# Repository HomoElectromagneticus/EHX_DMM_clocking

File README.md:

# EHX_DMM_clocking
This is a project to replace the original clock on an EHX Deluxe Memory man with something more capable.

The micro used is a PIC16F18326. It's NCO peripheral will be extremely useful for clock generation.

# License
CC BY-NC-SA https://creativecommons.org/licenses/by-nc-sa/4.0/

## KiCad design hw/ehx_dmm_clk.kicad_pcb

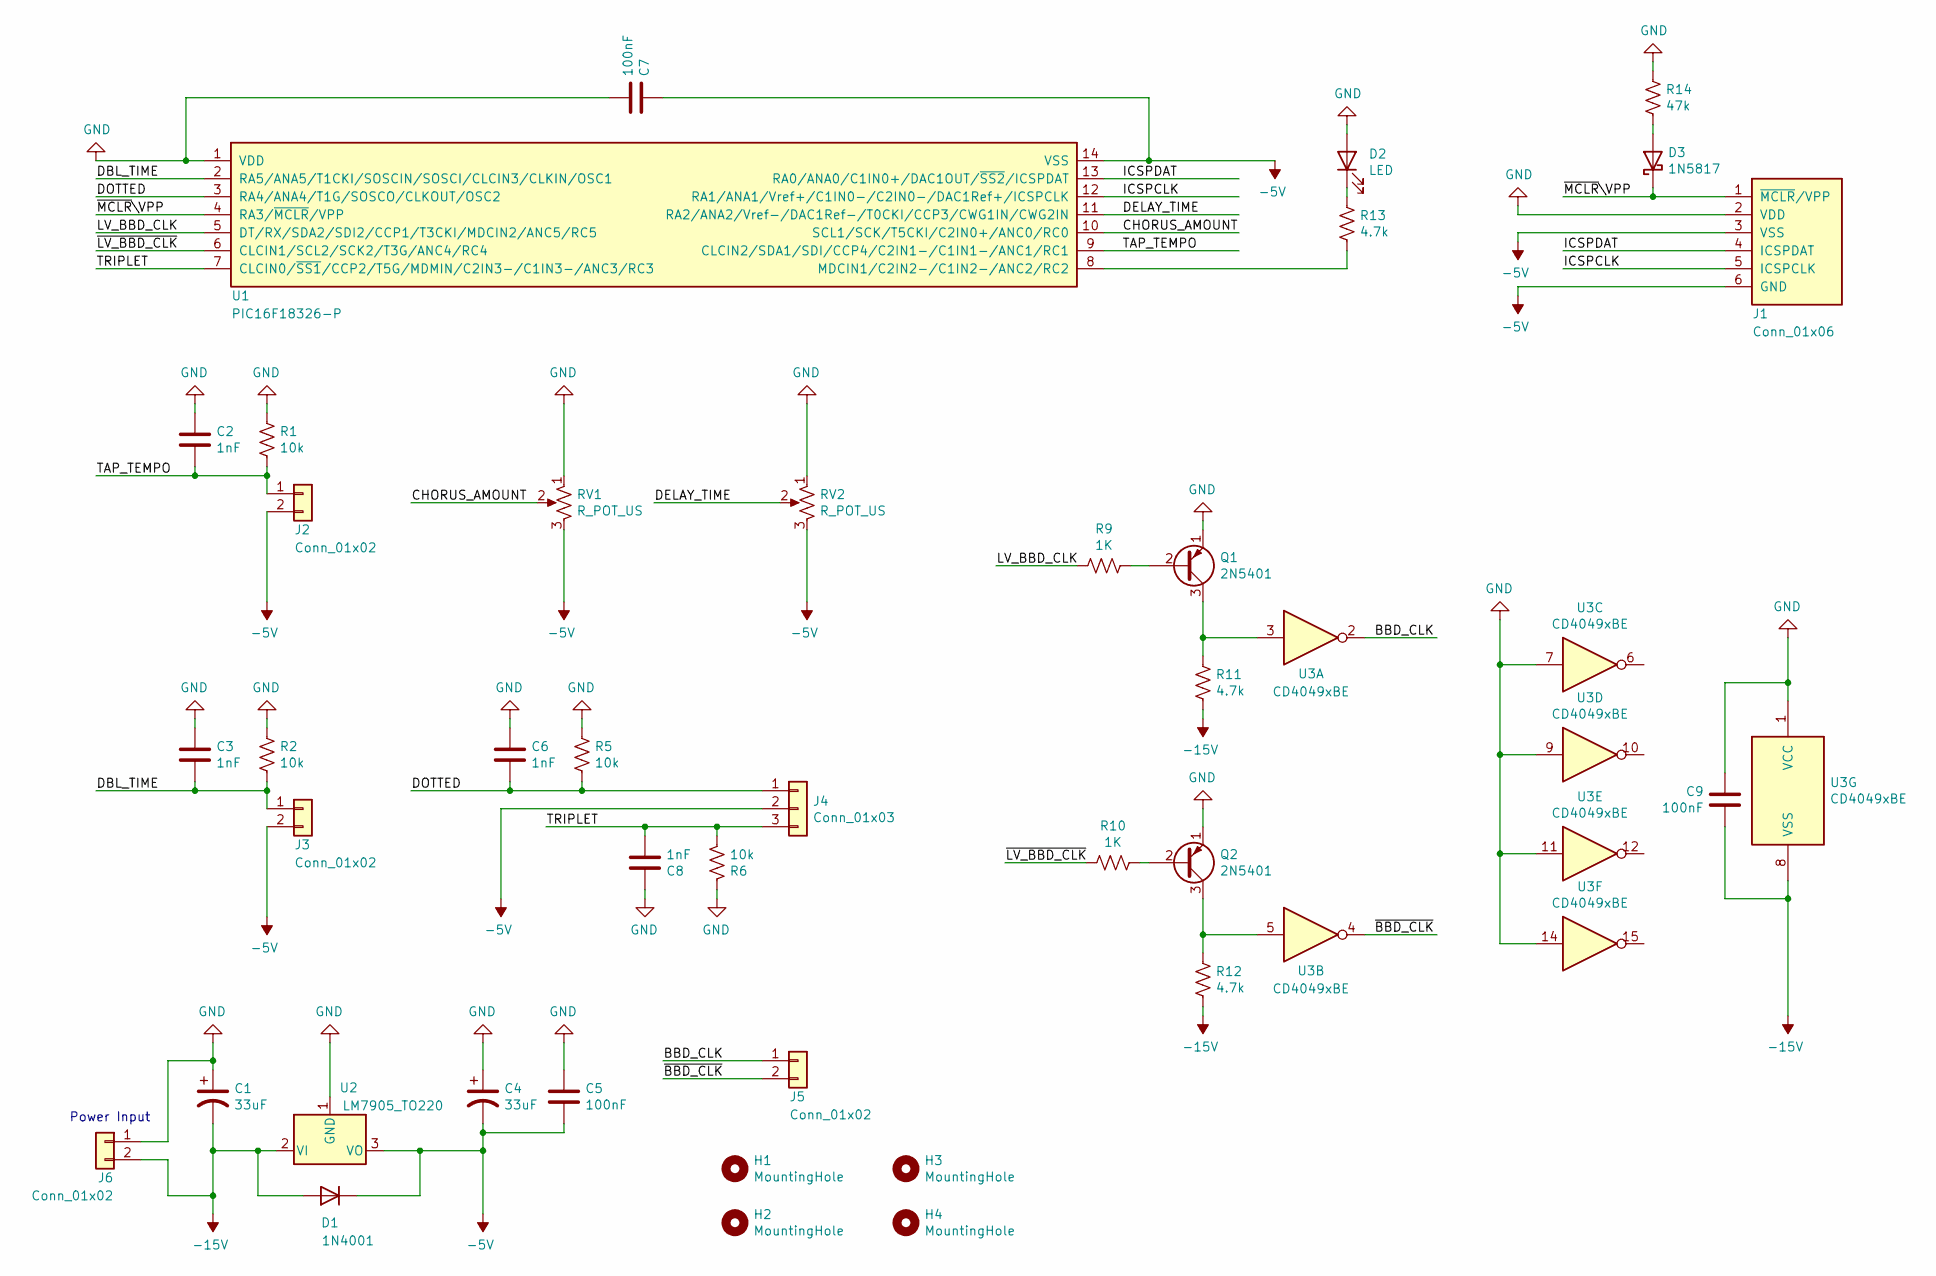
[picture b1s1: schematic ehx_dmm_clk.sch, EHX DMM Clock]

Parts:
C1, C4: 33uF; CP_Radial_D8.0mm_P2.50mm
C2, C3, C6, C8: 1nF; C_Rect_L7.0mm_W2.5mm_P5.00mm
C5, C7, C9: 100nF; C_Rect_L10.0mm_W3.0mm_P7.50mm_FKS3_FKP3
D1: 1N4001; D_DO-41_SOD81_P10.16mm_Horizontal
D2: LED; LED_D3.0mm
D3: 1N5817; D_DO-41_SOD81_P10.16mm_Horizontal
H1, H2, H3, H4: MountingHole; MountingHole_3mm
J1: Conn_01x06; PinHeader_1x06_P2.54mm_Vertical
J2, J3, J5, J6: Conn_01x02; PinHeader_1x02_P2.54mm_Vertical
J4: Conn_01x03; PinHeader_1x03_P2.54mm_Vertical
Q1, Q2: 2N5401; TO-92_HandSolder
R1, R2, R5, R6: 10k; R_Axial_DIN0207_L6.3mm_D2.5mm_P2.54mm_Vertical
R9, R10: 1K; R_Axial_DIN0207_L6.3mm_D2.5mm_P2.54mm_Vertical
R11, R12, R13: 4.7k; R_Axial_DIN0207_L6.3mm_D2.5mm_P2.54mm_Vertical
R14: 47k; R_Axial_DIN0207_L6.3mm_D2.5mm_P2.54mm_Vertical
RV1, RV2: R_POT_US; PinHeader_1x03_P2.54mm_Vertical
U1: PIC16F18326-P; DIP-14_W7.62mm_LongPads
U2: LM7905_TO220; TO-220-3_Vertical
U3: CD4049xBE; DIP-16_W7.62mm_LongPads

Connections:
-5V: C4.2, C5.2, C7.1, D1.1 (K), J1.3 (VSS), J1.6 (GND), J2.2, J3.2, J4.2, RV1.3, RV2.3, U1.14 (VSS), U2.3 (VO)
-15V: C1.2, C9.2, D1.2 (A), J6.2, R11.2, R12.2, U2.2 (VI), U3.8 (VSS)
/BBD_CLK: J5.1, U3.2
/CHORUS_AMOUNT: RV1.2, U1.10 (SCL1/SCK/T5CKI/C2IN0+/ANC0/RC0)
/DBL_TIME: C3.2, J3.1, R2.2, U1.2 (RA5/ANA5/T1CKI/SOSCIN/SOSCI/CLCIN3/CLKI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)
/DELAY_TIME: RV2.2, U1.11 (RA2/ANA2/Vref-/DAC1Ref-/T0CKI/CCP3/CWG1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)
/DOTTED: C6.2, J4.1, R5.2, U1.3 (RA4/ANA4/T1G/SOSCO/CLKOUT/OSC2)
/ICSPCLK: J1.5 (ICSPCLK), U1.12 (RA1/ANA1/Vref+/C1IN0-/C2IN0-/DAC1Ref+/I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)
/ICSPDAT: J1.4 (ICSPDAT), U1.13 (RA0/ANA0/C1IN0+/DAC1OUT/~SS2~/ICSPDAT)
/LV_BBD_CLK: R9.2, U1.5 (DT/RX/SDA2/SDI2/CCP1/T3CKI/MDCIN2/ANC5/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)
/TAP_TEMPO: C2.2, J2.1, R1.2, U1.9 (CLCIN2/SDA1/SDI/CCP4/C2IN1-/C1IN1-/ANC1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)
/TRIPLET: C8.2, J4.3, R6.2, U1.7 (CLCIN0/~SS1~/CCP2/T5G/MDMIN/C2IN3-/C1IN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)
/~BBD_CLK: J5.2, U3.4
/~LV_BBD_CLK: R10.2, U1.6 (CLCIN1/SCL2/SCK2/T3G/ANC4/RC4)
/~MCLR~\VPP: D3.1 (K), J1.1 (~MCLR~/VPP), U1.4 (RA3/~MCLR~/VPP)
GND: C1.1, C2.1, C3.1, C4.1, C5.1, C6.1, C7.2, C8.1, C9.1, D2.2 (A), J1.2 (VDD), J6.1, Q1.1 (E), Q2.1 (E), R1.1, R2.1, R5.1, R6.1, R14.1, RV1.1, RV2.1, U1.1 (VDD), U2.1 (GND), U3.1 (VCC), U3.7, U3.9, U3.11, U3.14
unnamed: D2.1 (K), R13.1
unnamed: D3.2 (A), R14.2
unnamed: Q1.2 (B), R9.1
unnamed: Q1.3 (C), R11.1, U3.3
unnamed: Q2.2 (B), R10.1
unnamed: Q2.3 (C), R12.1, U3.5
unnamed: R13.2, U1.8 (MDCIN1/C2IN2-/C1IN2-/ANC2/RC2)

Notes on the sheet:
Power Input

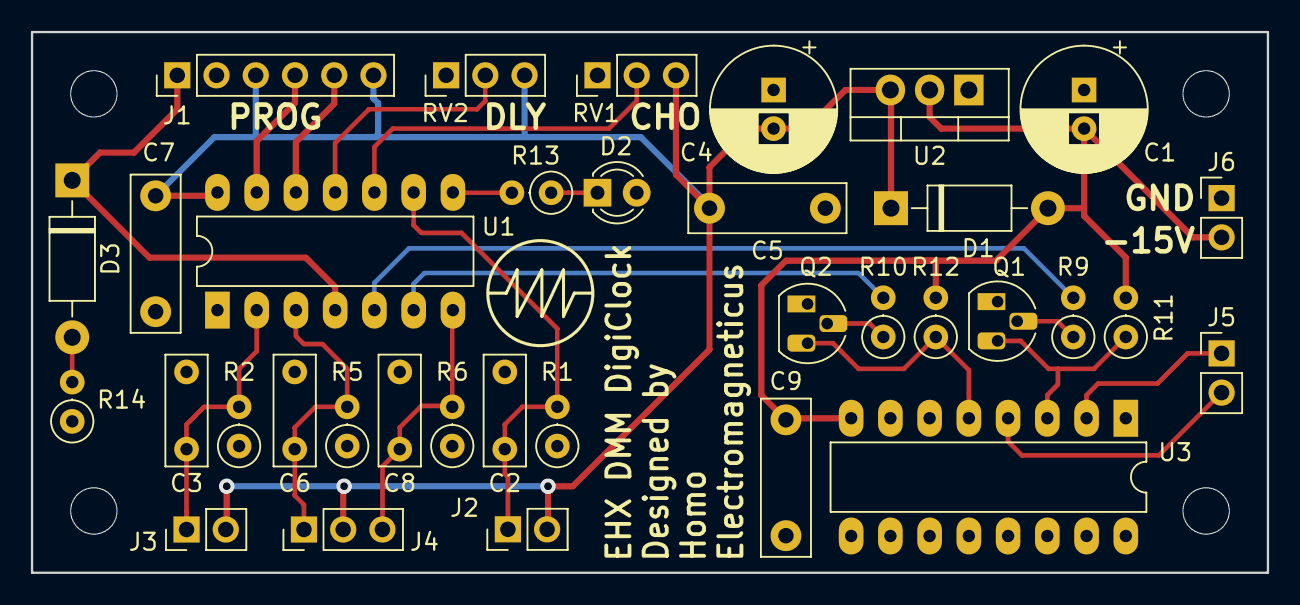
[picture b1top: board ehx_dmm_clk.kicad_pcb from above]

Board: 2 copper layers, 80.0 x 35.0 mm, 39 parts (0 on the bottom side), 23 nets.

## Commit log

2020-03-23 Initial commit for this project to replace the clock on an EHX Deluxe Memory Man
2020-03-23 Very early draft of the code - just basic clock generation with frequency controlled by a pot
2020-07-10 Switched the project over to the PIC16F18326 since that part has an NCO
2020-07-12 ADC, NCO, and CWG are all working
2020-07-12 Added some calculations about the BBD clocks and delay time
2020-07-12 Update README.md
    Added a note about the micro used.
2020-07-12 Added a variable to store the tap tempo button state. Also tweaked the timer2 interrupt freq so that the potentiometer is scanned 10x a second instead of 7x.
2020-07-12 Set the ignore file to ignore my local development scratchpad
2020-07-12 Added a button debounce routing using Timer4. I have the debounced button signal driving an LED right now for debugging purposes.
2020-07-12 fixed a comment about the ADC convertion time
2020-07-13 Button debouncing works. Tap tempo needs a lot of work still, but periodic button pushing does change the output clock frequency...
2020-07-13 Added limits to the NCO frequency so that weird tap tempo entries don't break the clock output
2020-07-18 Lots of changes. Tap tempo appears to be working!
2020-07-18 Made a lot of changes to how I was looking at the clock calculations.
2020-07-18 Significantly optimized the tap tempo --> output clock rate calculation. Added a way to switch from tap tempo mode to 'delay time controlled by the knob' mode.
2020-07-18 Added another sheet to the clock calculations document
2020-07-18 Slowed down the ADC converstion rate to get more accurate readings. The system has the time to allot for this.
2020-07-18 Added a sheet to help scale the ADC readings of knob position into NCO increment values for the output clock
2020-07-18 Scaled the ADC readings into the 'stock range' of the DMM
2020-08-01 Added the correct MPLAB X files, updated the gitignore
2020-08-02 Initial refactor complete. Code ready for a chorus LFO
2020-08-02 removed an unused variable
2020-08-02 Setup ADC channel switching so that the chorus amount knob can be read in addition to the delay time knob
2020-08-02 Updated the clock calculations file to support the new way the code works for the delay knob.
2020-08-03 Made quite a few changes to get the chorus LFO working right. Had the bring the NCO source clock frequency down by half, but this gives the program more resolution anyway. The chorus function works, 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
2020-08-10 The chorus amount is now a percentage of the delay time, which is much more natural feeling.
2020-08-24 Added some labels for tap tempo time division symbols
2020-08-24 Updated gitignore to accomodate kicad files
2020-08-24 Initial commit of the electrical design. So far, it's just a schematic.
2020-08-24 Did a bit of reorganization for just the project documentation
2020-08-24 Did some reoganizing of the firmware files
2020-08-24 Added license details to project and code
2020-08-24 Schematic annotated
2020-08-24 Footprint assignment complete
2020-08-24 Added connections for power input and clock output
2020-08-24 Initial commit of the PCB
2020-08-24 Removed some unnecessary resistors
2020-08-24 Initial work on the PCBA layout
2020-08-25 Initial PCB floorplanning complete
2020-08-25 Added some mounting holes
2020-09-07 Huge commit. Major changes to board size, layout, footprints, etc. All to get the design to fit into the enclosure

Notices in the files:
hw/ehx_dmm_clk.kicad_pcb:
CC BY-NC-SA 4.0
